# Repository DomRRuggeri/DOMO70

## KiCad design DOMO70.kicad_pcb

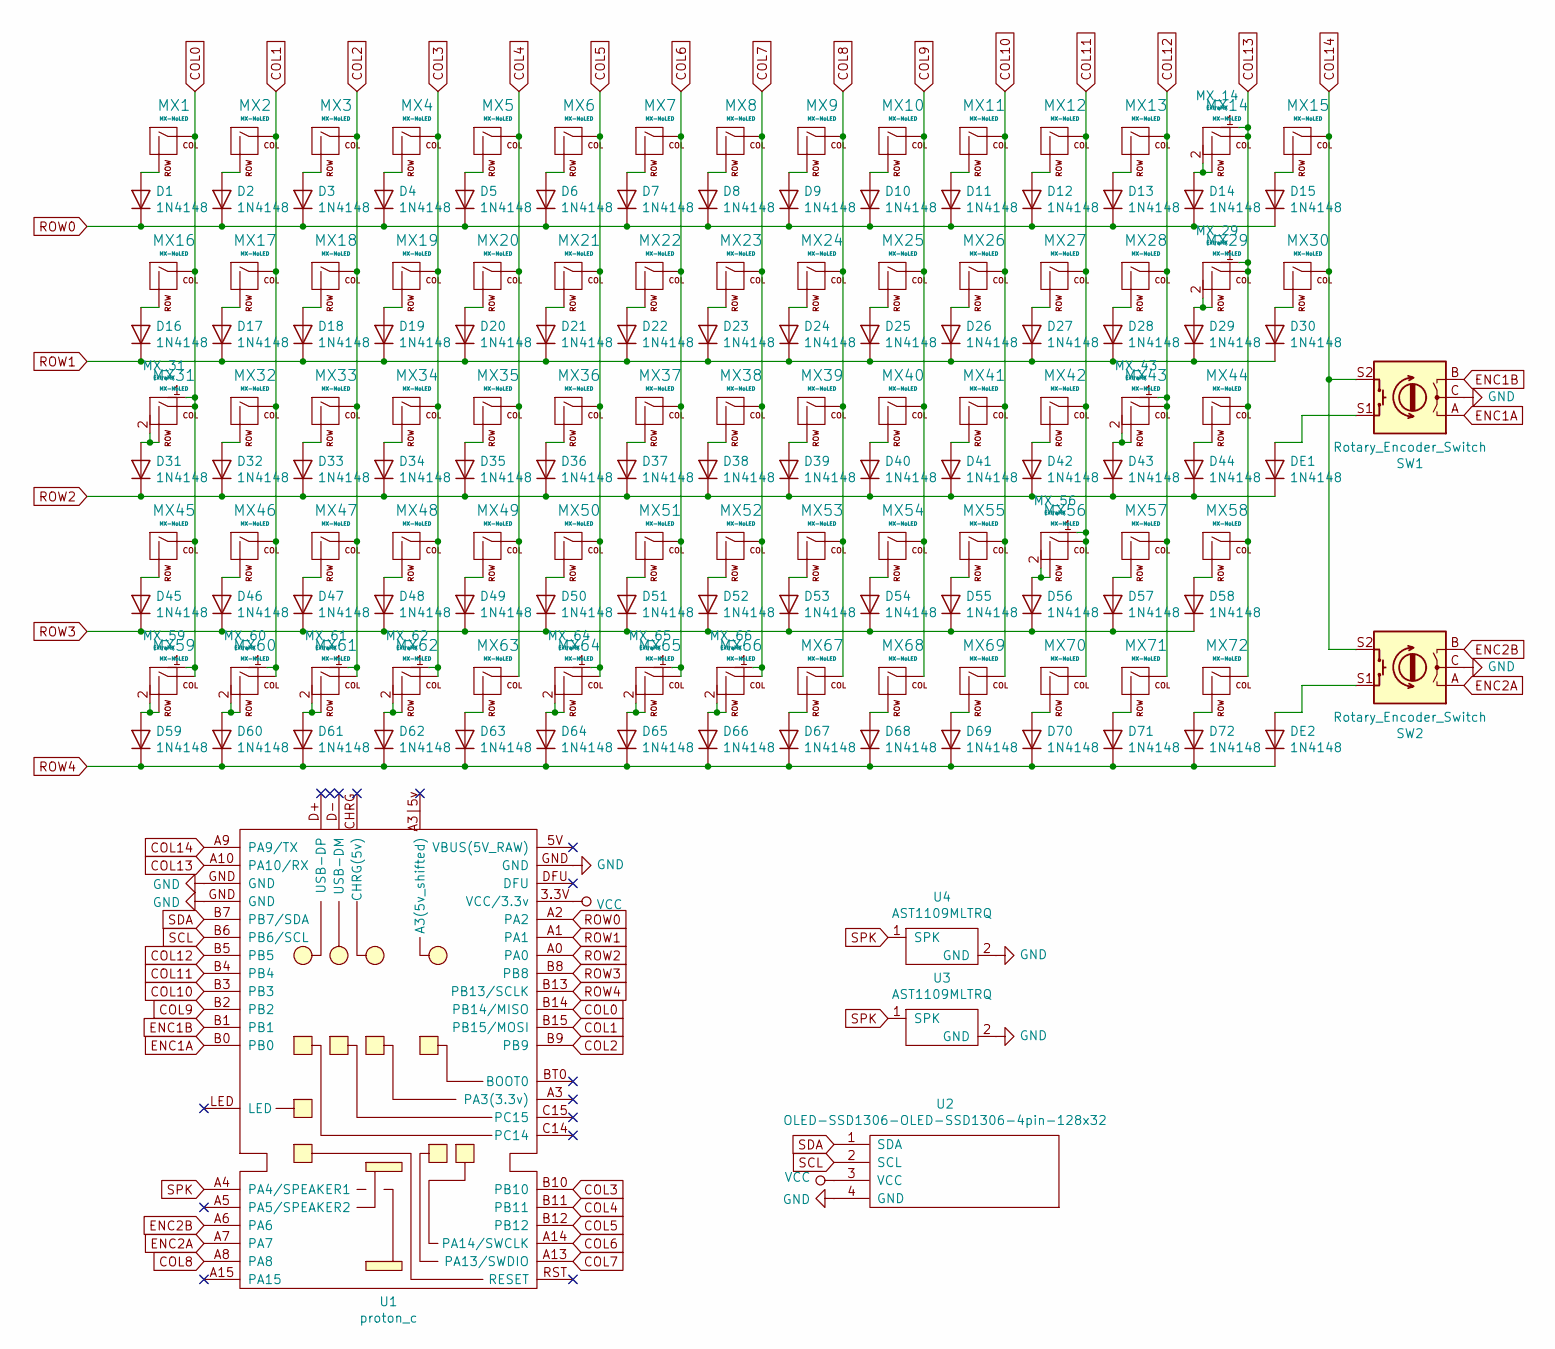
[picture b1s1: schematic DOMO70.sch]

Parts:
D1, D2, D3, D4, D5, D6, D7, D8, D9, D10, D11, D12, D13, D14, D15, D16, D17, D18, D19, D20, D21, D22, D23, D24, D25, D26, D27, D28, D29, D30, D31, D32, D33, D34, D35, D36, D37, D38, D39, D40, D41, D42, D43, D44, D45, D46, D47, D48, D49, D50, D51, D52, D53, D54, D55, D56, D57, D58, D59, D60, D61, D62, D63, D64, D65, D66, D67, D68, D69, D70, D71, D72: 1N4148; D_DO-35_SOD27_P5.08mm_Horizontal
DE1, DE2: 1N4148; D_DO-35_SOD27_P5.08mm_Horizontal
MX1, MX2, MX3, MX4, MX5, MX6, MX7, MX8, MX9, MX10, MX11, MX12, MX13, MX14, MX15, MX17, MX18, MX19, MX20, MX21, MX22, MX23, MX24, MX25, MX26, MX27, MX28, MX30, MX32, MX33, MX34, MX35, MX36, MX37, MX38, MX39, MX40, MX41, MX42, MX44, MX46, MX47, MX48, MX49, MX50, MX51, MX52, MX53, MX54, MX55, MX57, MX58, MX67, MX68, MX69, MX70, MX71, MX72: MX-NoLED; MXOnly-1U-NoLED
MX16, MX29: MX-NoLED; MXOnly-1.5U-NoLED
MX31: MX-NoLED; MXOnly-1.75U-NoLED
MX43, MX45: MX-NoLED; MXOnly-2.25U-NoLED
MX56: MX-NoLED; MXOnly-2.75U-NoLED
MX59, MX60, MX61, MX63, MX64, MX65, MX66: MX-NoLED; MXOnly-1.25U-NoLED
MX62: MX-NoLED; MXOnly-6.25U-ReversedStabilizers-NoLED
MX_14: ExtraMX; MXOnly-2U-NoLED
MX_29: ExtraMX; MXOnly-ISO-ReversedStabilizers
MX_31: ExtraMX; MXOnly-1.25U-NoLED
MX_43, MX_60, MX_65: ExtraMX; MXOnly-1U-NoLED
MX_56: ExtraMX; MXOnly-1.75U-NoLED
MX_59, MX_61, MX_64, MX_66: ExtraMX; MXOnly-1.5U-NoLED
MX_62: ExtraMX; MXOnly-7U-ReversedStabilizers-NoLED
SW1, SW2: Rotary_Encoder_Switch; RotaryEncoder_Alps_EC11E-Switch_Vertical_H20mm
U1: proton_c
U2: OLED-SSD1306-OLED-SSD1306-4pin-128x32; OLED-1306-Supports
U3, U4: AST1109MLTRQ; Buzzer_Mallory_AST1109MLTRQ

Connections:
COL0: MX1.1 (COL), MX16.1 (COL), MX31.1 (COL), MX45.1 (COL), MX59.1 (COL), MX_31.1, MX_59.1, U1.B14 (PB14/MISO)
COL1: MX2.1 (COL), MX17.1 (COL), MX32.1 (COL), MX46.1 (COL), MX60.1 (COL), MX_60.1, U1.B15 (PB15/MOSI)
COL2: MX3.1 (COL), MX18.1 (COL), MX33.1 (COL), MX47.1 (COL), MX61.1 (COL), MX_61.1, U1.B9
COL3: MX4.1 (COL), MX19.1 (COL), MX34.1 (COL), MX48.1 (COL), MX62.1 (COL), MX_62.1, U1.B10
COL4: MX5.1 (COL), MX20.1 (COL), MX35.1 (COL), MX49.1 (COL), MX63.1 (COL), U1.B11
COL5: MX6.1 (COL), MX21.1 (COL), MX36.1 (COL), MX50.1 (COL), MX64.1 (COL), MX_64.1, U1.B12
COL6: MX7.1 (COL), MX22.1 (COL), MX37.1 (COL), MX51.1 (COL), MX65.1 (COL), MX_65.1, U1.A14 (PA14/SWCLK)
COL7: MX8.1 (COL), MX23.1 (COL), MX38.1 (COL), MX52.1 (COL), MX66.1 (COL), MX_66.1, U1.A13 (PA13/SWDIO)
COL8: MX9.1 (COL), MX24.1 (COL), MX39.1 (COL), MX53.1 (COL), MX67.1 (COL), U1.A8
COL9: MX10.1 (COL), MX25.1 (COL), MX40.1 (COL), MX54.1 (COL), MX68.1 (COL), U1.B2
COL10: MX11.1 (COL), MX26.1 (COL), MX41.1 (COL), MX55.1 (COL), MX69.1 (COL), U1.B3
COL11: MX12.1 (COL), MX27.1 (COL), MX42.1 (COL), MX56.1 (COL), MX70.1 (COL), MX_56.1, U1.B4
COL12: MX13.1 (COL), MX28.1 (COL), MX43.1 (COL), MX57.1 (COL), MX71.1 (COL), MX_43.1, U1.B5
COL13: MX14.1 (COL), MX29.1 (COL), MX44.1 (COL), MX58.1 (COL), MX72.1 (COL), MX_14.1, MX_29.1, U1.A10 (PA10/RX)
COL14: MX15.1 (COL), MX30.1 (COL), SW1.S2, SW2.S2, U1.A9 (PA9/TX)
ENC1A: SW1.A, U1.B0
ENC1B: SW1.B, U1.B1
ENC2A: SW2.A, U1.A7
ENC2B: SW2.B, U1.A6
GND: SW1.C, SW2.C, U1.GND, U2.4 (GND), U3.2 (GND), U4.2 (GND)
unnamed: D1.2 (A), MX1.2 (ROW)
unnamed: D2.2 (A), MX2.2 (ROW)
unnamed: D3.2 (A), MX3.2 (ROW)
unnamed: D4.2 (A), MX4.2 (ROW)
unnamed: D5.2 (A), MX5.2 (ROW)
unnamed: D6.2 (A), MX6.2 (ROW)
unnamed: D7.2 (A), MX7.2 (ROW)
unnamed: D8.2 (A), MX8.2 (ROW)
unnamed: D9.2 (A), MX9.2 (ROW)
unnamed: D10.2 (A), MX10.2 (ROW)
unnamed: D11.2 (A), MX11.2 (ROW)
unnamed: D12.2 (A), MX12.2 (ROW)
unnamed: D13.2 (A), MX13.2 (ROW)
unnamed: D14.2 (A), MX14.2 (ROW), MX_14.2
unnamed: D15.2 (A), MX15.2 (ROW)
unnamed: D16.2 (A), MX16.2 (ROW)
unnamed: D17.2 (A), MX17.2 (ROW)
unnamed: D18.2 (A), MX18.2 (ROW)
unnamed: D19.2 (A), MX19.2 (ROW)
unnamed: D20.2 (A), MX20.2 (ROW)
unnamed: D21.2 (A), MX21.2 (ROW)
unnamed: D22.2 (A), MX22.2 (ROW)
unnamed: D23.2 (A), MX23.2 (ROW)
unnamed: D24.2 (A), MX24.2 (ROW)
unnamed: D25.2 (A), MX25.2 (ROW)
unnamed: D26.2 (A), MX26.2 (ROW)
unnamed: D27.2 (A), MX27.2 (ROW)
unnamed: D28.2 (A), MX28.2 (ROW)
unnamed: D29.2 (A), MX29.2 (ROW), MX_29.2
unnamed: D30.2 (A), MX30.2 (ROW)
unnamed: D31.2 (A), MX31.2 (ROW), MX_31.2
unnamed: D32.2 (A), MX32.2 (ROW)
unnamed: D33.2 (A), MX33.2 (ROW)
unnamed: D34.2 (A), MX34.2 (ROW)
unnamed: D35.2 (A), MX35.2 (ROW)
unnamed: D36.2 (A), MX36.2 (ROW)
unnamed: D37.2 (A), MX37.2 (ROW)
unnamed: D38.2 (A), MX38.2 (ROW)
unnamed: D39.2 (A), MX39.2 (ROW)
unnamed: D40.2 (A), MX40.2 (ROW)
unnamed: D41.2 (A), MX41.2 (ROW)
unnamed: D42.2 (A), MX42.2 (ROW)
unnamed: D43.2 (A), MX43.2 (ROW), MX_43.2
unnamed: D44.2 (A), MX44.2 (ROW)
unnamed: D45.2 (A), MX45.2 (ROW)
unnamed: D46.2 (A), MX46.2 (ROW)
unnamed: D47.2 (A), MX47.2 (ROW)
unnamed: D48.2 (A), MX48.2 (ROW)
unnamed: D49.2 (A), MX49.2 (ROW)
unnamed: D50.2 (A), MX50.2 (ROW)
unnamed: D51.2 (A), MX51.2 (ROW)
unnamed: D52.2 (A), MX52.2 (ROW)
unnamed: D53.2 (A), MX53.2 (ROW)
unnamed: D54.2 (A), MX54.2 (ROW)
unnamed: D55.2 (A), MX55.2 (ROW)
unnamed: D56.2 (A), MX56.2 (ROW), MX_56.2
unnamed: D57.2 (A), MX57.2 (ROW)
unnamed: D58.2 (A), MX58.2 (ROW)
unnamed: D59.2 (A), MX59.2 (ROW), MX_59.2
unnamed: D60.2 (A), MX60.2 (ROW), MX_60.2
unnamed: D61.2 (A), MX61.2 (ROW), MX_61.2
unnamed: D62.2 (A), MX62.2 (ROW), MX_62.2
unnamed: D63.2 (A), MX63.2 (ROW)
unnamed: D64.2 (A), MX64.2 (ROW), MX_64.2
unnamed: D65.2 (A), MX65.2 (ROW), MX_65.2
unnamed: D66.2 (A), MX66.2 (ROW), MX_66.2
unnamed: D67.2 (A), MX67.2 (ROW)
unnamed: D68.2 (A), MX68.2 (ROW)
unnamed: D69.2 (A), MX69.2 (ROW)
unnamed: D70.2 (A), MX70.2 (ROW)
unnamed: D71.2 (A), MX71.2 (ROW)
unnamed: D72.2 (A), MX72.2 (ROW)
unnamed: DE1.2 (A), SW1.S1
unnamed: DE2.2 (A), SW2.S1
ROW0: D1.1 (K), D2.1 (K), D3.1 (K), D4.1 (K), D5.1 (K), D6.1 (K), D7.1 (K), D8.1 (K), D9.1 (K), D10.1 (K), D11.1 (K), D12.1 (K), D13.1 (K), D14.1 (K), D15.1 (K), U1.A2
ROW1: D16.1 (K), D17.1 (K), D18.1 (K), D19.1 (K), D20.1 (K), D21.1 (K), D22.1 (K), D23.1 (K), D24.1 (K), D25.1 (K), D26.1 (K), D27.1 (K), D28.1 (K), D29.1 (K), D30.1 (K), U1.A1
ROW2: D31.1 (K), D32.1 (K), D33.1 (K), D34.1 (K), D35.1 (K), D36.1 (K), D37.1 (K), D38.1 (K), D39.1 (K), D40.1 (K), D41.1 (K), D42.1 (K), D43.1 (K), D44.1 (K), DE1.1 (K), U1.A0
ROW3: D45.1 (K), D46.1 (K), D47.1 (K), D48.1 (K), D49.1 (K), D50.1 (K), D51.1 (K), D52.1 (K), D53.1 (K), D54.1 (K), D55.1 (K), D56.1 (K), D57.1 (K), D58.1 (K), U1.B8
ROW4: D59.1 (K), D60.1 (K), D61.1 (K), D62.1 (K), D63.1 (K), D64.1 (K), D65.1 (K), D66.1 (K), D67.1 (K), D68.1 (K), D69.1 (K), D70.1 (K), D71.1 (K), D72.1 (K), DE2.1 (K), U1.B13 (PB13/SCLK)
SCL: U1.B6 (PB6/SCL), U2.2 (SCL)
SDA: U1.B7 (PB7/SDA), U2.1 (SDA)
SPK: U1.A4 (PA4/SPEAKER1), U3.1 (SPK), U4.1 (SPK)
VCC: U1.3.3V (VCC/3.3v), U2.3 (VCC)

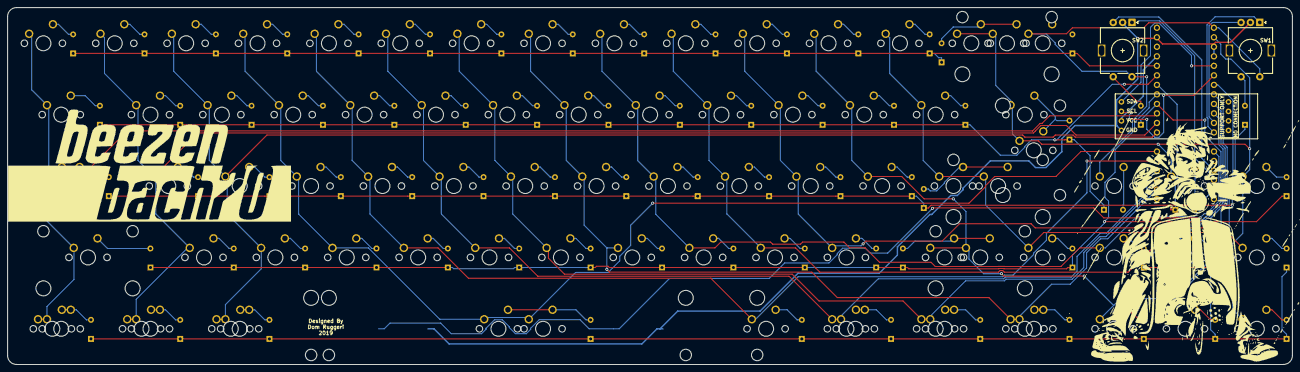
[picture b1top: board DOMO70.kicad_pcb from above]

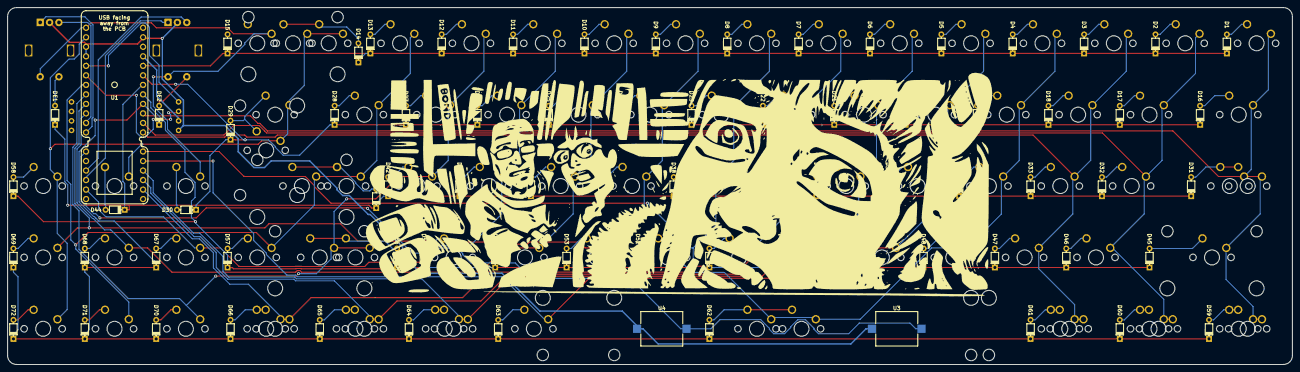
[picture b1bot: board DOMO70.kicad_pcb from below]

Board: 2 copper layers, 342.9 x 95.3 mm, 164 parts (77 on the bottom side), 103 nets.

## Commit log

2019-12-21 Initial commit. Let's do this.
2019-12-21 Added submodules
2019-12-21 Moved project folder up a level.
2019-12-21 Layed down groundwork for schematic.
2019-12-28 First Real Schematic
2020-01-01 Messing with matrix
2020-01-01 Created speaker footprint/symbol
2020-01-06 Added routing
2020-01-06 Added more routing
2020-09-11 Updating who-knows-what
2020-09-12 Added routes, graphics
2020-09-14 More graphics
